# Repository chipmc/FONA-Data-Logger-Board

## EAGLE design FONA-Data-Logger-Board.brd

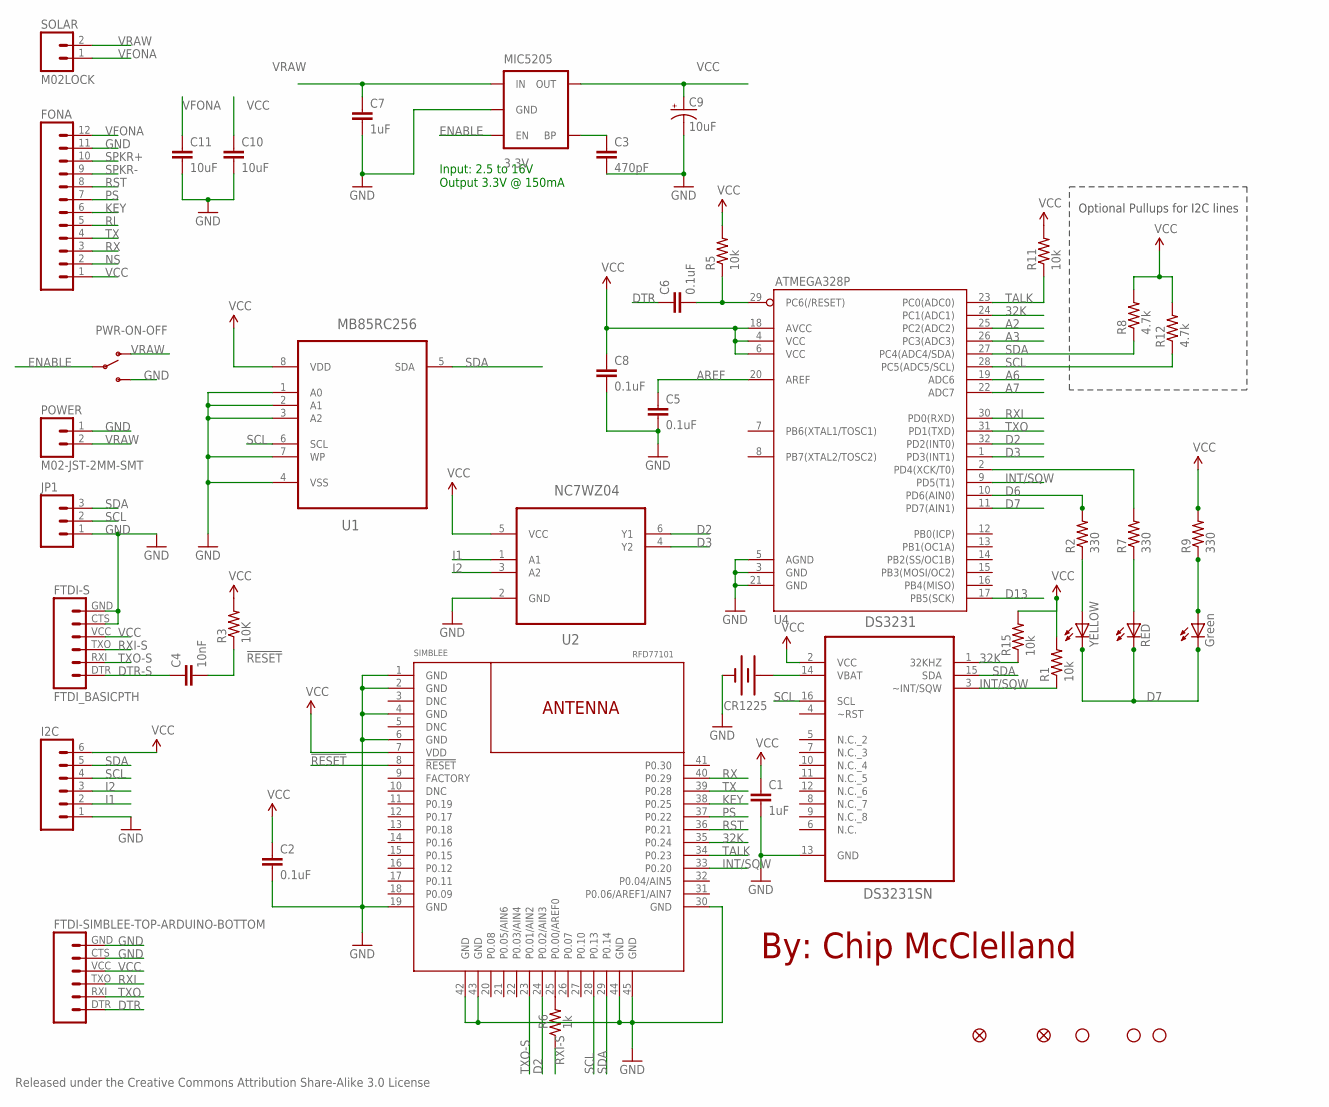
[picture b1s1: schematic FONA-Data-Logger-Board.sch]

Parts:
ATMEGA328P: U4; TQFP32-08
C1, C7: 1uF; 0805
C2, C5, C6, C8: 0.1uF; 0805
C3: 470pF; 0805
C4: 10nF; 0805
C9: 10uF; EIA3216
C10, C11: 10uF; 0805
CR1225: BATTERY12MM; BATTCON_12MM
DS3231: DS3231SN; SOIC127P1032X265-16N
FID1, FID2: FIDUCIALUFIDUCIAL; MICRO-FIDUCIAL
FONA: M12PTH; 1X12
FTDI-S: FTDI_BASICPTH; FTDI_BASIC
FTDI-SIMBLEE-TOP-ARDUINO-BOTTOM: FTDI Basic; FTDI_BASIC
G: Green; CHIPLED_0805
I2C: M06LOCK; 1X06_LOCK
JP1: M03LOCK; 1X03_LOCK
JP3, JP4, JP6: STAND-OFF
MB85RC256: U1; SOIC127P600X175-8N
MIC5205: 3.3V; SOT23-5
NC7WZ04: U2; SOT65P210X110-6N
POWER: M02-JST-2MM-SMT; JST-2-SMD
PWR-ON-OFF: SWITCH-SPDTPTH; SWITCH-SPDT
R: RED; CHIPLED_0805
R1, R5, R11, R15: 10k; 0805
R2, R7, R9: 330; 0603-RES
R3: 10K; 0805
R6: 1k; 0805
R8, R12: 4.7k; 0805
SIMBLEE: RFD77101
SOLAR: M02LOCK; 1X02_LOCK
Y: YELLOW; CHIPLED_0805

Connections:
32K: ATMEGA328P.24 (PC1(ADC1)), DS3231.1 (32KHZ), R15.1, SIMBLEE.35 (P0.24)
!RESET: C4.2, R3.1, SIMBLEE.8 (!RESET!)
A2: ATMEGA328P.25 (PC2(ADC2))
A3: ATMEGA328P.26 (PC3(ADC3))
A6: ATMEGA328P.19 (ADC6)
A7: ATMEGA328P.22 (ADC7)
AREF: ATMEGA328P.20 (AREF), C5.1
D2: ATMEGA328P.32 (PD2(INT0)), NC7WZ04.6 (Y1), SIMBLEE.24 (P0.02/AIN3)
D3: ATMEGA328P.1 (PD3(INT1)), NC7WZ04.4 (Y2)
D6: ATMEGA328P.10 (PD6(AIN0)), R2.2
D7: ATMEGA328P.11 (PD7(AIN1)), G.C, R.C, Y.C
D13: ATMEGA328P.17 (PB5(SCK))
DTR: C6.1, FTDI-SIMBLEE-TOP-ARDUINO-BOTTOM.DTR (1)
DTR-S: C4.1, FTDI-S.DTR (1)
ENABLE: MIC5205.3 (EN), PWR-ON-OFF.2
GND: ATMEGA328P.3 (GND), ATMEGA328P.5 (AGND), ATMEGA328P.21 (GND), C1.2, C2.2, C3.2, C5.2, C7.2, C8.2, C9.C (-), C10.2, C11.2, CR1225.GND (-), DS3231.13 (GND), FONA.11, FTDI-S.CTS (5), FTDI-S.GND (6), FTDI-SIMBLEE-TOP-ARDUINO-BOTTOM.CTS (5), FTDI-SIMBLEE-TOP-ARDUINO-BOTTOM.GND (6), I2C.1, JP1.1, MB85RC256.1 (A0), MB85RC256.2 (A1), MB85RC256.3 (A2), MB85RC256.4 (VSS), MB85RC256.7 (WP), MIC5205.2 (GND), NC7WZ04.2 (GND), POWER.1 (2), PWR-ON-OFF.3 (S), SIMBLEE.1 (GND), SIMBLEE.2 (GND), SIMBLEE.4 (GND), SIMBLEE.6 (GND), SIMBLEE.19 (GND), SIMBLEE.30 (GND), SIMBLEE.42 (GND), SIMBLEE.43 (GND), SIMBLEE.44 (GND), SIMBLEE.45 (GND)
I1: I2C.2, NC7WZ04.1 (A1)
I2: I2C.3, NC7WZ04.3 (A2)
INT/SQW: ATMEGA328P.9 (PD5(T1)), DS3231.3 (~INT/SQW), R1.1, SIMBLEE.33 (P0.20)
KEY: FONA.6, SIMBLEE.38 (P0.25)
unnamed: R2.1, Y.A
unnamed: C3.1, MIC5205.4 (BP)
unnamed: ATMEGA328P.2 (PD4(XCK/T0)), R7.2
unnamed: R.A, R7.1
unnamed: R6.2, SIMBLEE.25 (P0.00/AREF0)
unnamed: G.A, R9.1
NS: FONA.2
PS: FONA.7, SIMBLEE.37 (P0.22)
RESET: ATMEGA328P.29 (PC6(/RESET)), C6.2, R5.1
RI: FONA.5
RST: FONA.8, SIMBLEE.36 (P0.21)
RX: FONA.3, SIMBLEE.40 (P0.29)
RXI: ATMEGA328P.30 (PD0(RXD)), FTDI-SIMBLEE-TOP-ARDUINO-BOTTOM.TXO (3)
RXI-S: FTDI-S.TXO (3), R6.1
SCL: ATMEGA328P.28 (PC5(ADC5/SCL)), DS3231.16 (SCL), I2C.4, JP1.2, MB85RC256.6 (SCL), R12.1, SIMBLEE.28 (P0.13)
SDA: ATMEGA328P.27 (PC4(ADC4/SDA)), DS3231.15 (SDA), I2C.5, JP1.3, MB85RC256.5 (SDA), R8.1, SIMBLEE.29 (P0.14)
SPKR+: FONA.10
SPKR-: FONA.9
TALK: ATMEGA328P.23 (PC0(ADC0)), R11.1, SIMBLEE.34 (P0.23)
TX: FONA.4, SIMBLEE.39 (P0.28)
TXO: ATMEGA328P.31 (PD1(TXD)), FTDI-SIMBLEE-TOP-ARDUINO-BOTTOM.RXI (2)
TXO-S: FTDI-S.RXI (2), SIMBLEE.23 (P0.01/AIN2)
VBAT: CR1225.PWR@1 (+), DS3231.14 (VBAT)
VCC: ATMEGA328P.4 (VCC), ATMEGA328P.6 (VCC), ATMEGA328P.18 (AVCC), C1.1, C2.1, C8.1, C9.A (+), C10.1, DS3231.2 (VCC), FONA.1, FTDI-S.VCC (4), FTDI-SIMBLEE-TOP-ARDUINO-BOTTOM.VCC (4), I2C.6, MB85RC256.8 (VDD), MIC5205.5 (OUT), NC7WZ04.5 (VCC), R1.2, R3.2, R5.2, R8.2, R9.2, R11.2, R12.2, R15.2, SIMBLEE.7 (VDD)
VFONA: C11.1, FONA.12, SOLAR.1
VRAW: C7.1, MIC5205.1 (IN), POWER.2 (1), PWR-ON-OFF.1 (O), SOLAR.2

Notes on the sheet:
Released under the Creative Commons Attribution Share-Alike 3.0 License
Optional Pullups for I2C lines
By: Chip McClelland
Input: 2.5 to 16V Output 3.3V @ 150mA

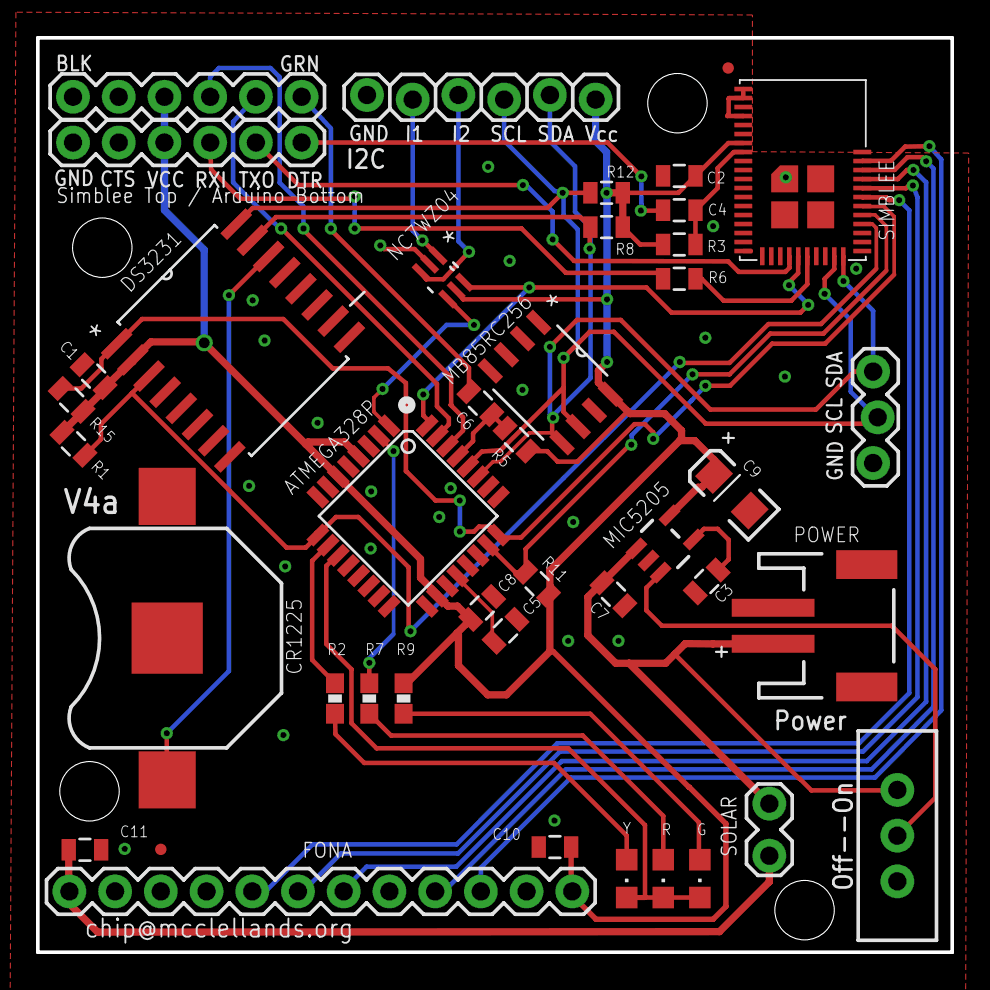
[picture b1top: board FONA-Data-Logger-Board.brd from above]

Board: 2 copper layers, 50.8 x 50.8 mm, 46 parts (0 on the bottom side), 37 nets.

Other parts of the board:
JP2: STAND-OFF

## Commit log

2016-05-09 Initial Commit
    EAGLE Files sent to OSHPark on 5 May 2016
2016-05-09 Updated the Board and Schematic - Minor

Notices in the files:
parts and their libraries:
SparkFun-Connectors: Licensing: CC v3.0 Share-Alike You are welcome to use this library for commercial purposes.
SparkFun-Resistors: Licensing: Creative Commons ShareAlike 4.0 International - https://creativecommons.org/licenses/by-sa/4.0
RFDigital: © 2015 RF Digital Corporation
